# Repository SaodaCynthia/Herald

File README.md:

# Herald

Herald is a solar energy harvesting room number transmitter BLE beacon. It has been tested and deployed in 3 different indoor settings: a lab space with sunlight , indoor office with only indoor lights and an industrial steam plant with indoor lights. This project shows that solar energy harvesting beacons has promising future in indoor settings and performance can be further improved with planned deployment of beacons and a minimum indoor light intensity level.

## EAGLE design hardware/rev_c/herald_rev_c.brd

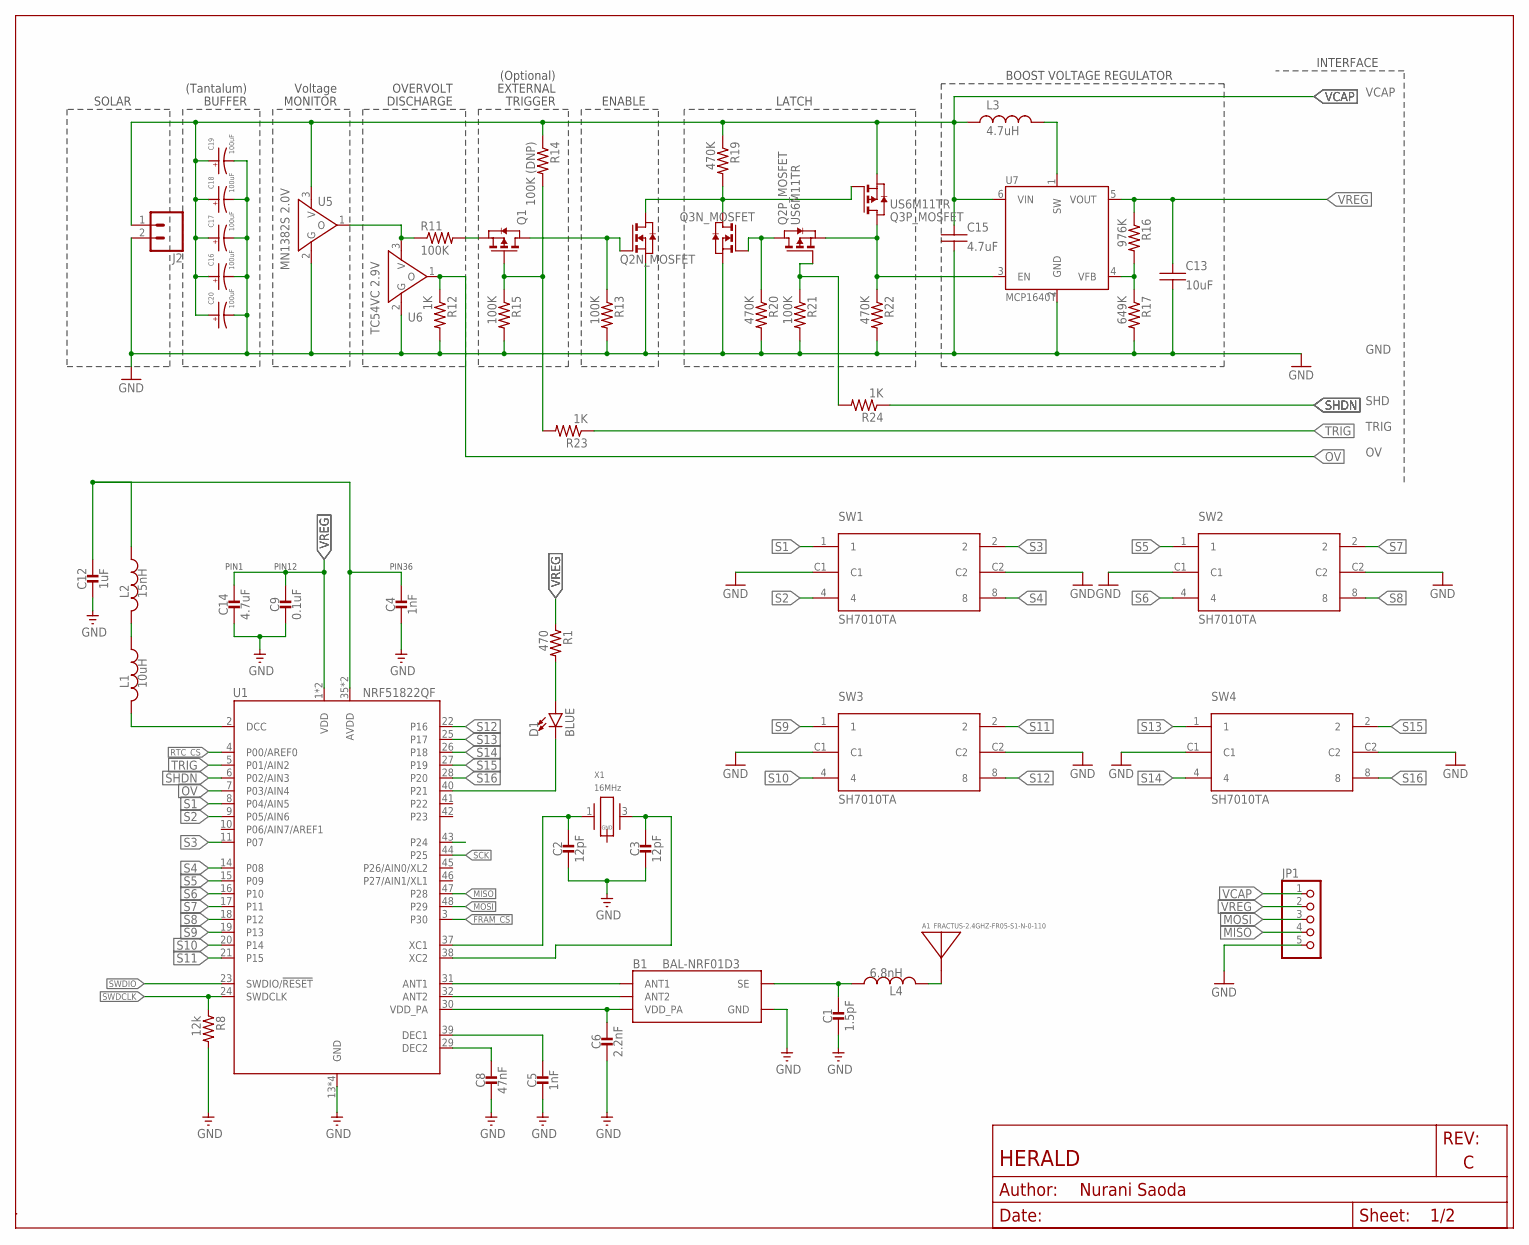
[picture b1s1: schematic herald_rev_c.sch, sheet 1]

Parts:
A1: FRACTUS-2.4GHZ-FR05-S1-N-0-110; FRACTUS-ANTENNA-FR05-S1-N-0-110
B1: BAL-NRF01D3
C1: 1.5pF; 0402_CAP
C2, C3: 12pF; 0402_CAP
C4, C5: 1nF; 0402_CAP
C6: 2.2nF; 0402_CAP
C8: 47nF; 0402_CAP
C9: 0.1uF; 0402_CAP
C12: 1uF; 0402_CAP
C13: 10uF; R0603B
C14: 4.7uF; 0402_CAP
C15: 4.7uF; R0603B
C16, C17, C18, C19, C20: 100uF; CAP1210
D1: BLUE; LED-0603
J2: CONN_02; 1X02
JP1: PINHD-1X5; 1X05
L1: 10uH; 0603_CAP; DIGIKEY 490-4025-1-ND
L2: 15nH; 0402_CAP; DIGIKEY 587-1521-1-ND
L3: 4.7uH; L2828
L4: 6.8nH; 0402_CAP; DIGIKEY 587-1521-1-ND
Q1: PMOSSOT23; SOT-23
Q2, Q3: US6M11TR; TUMT6
R1: 470; 0402_RES; DIGIKEY RHM470CECT-ND
R8: 12k; 0402_RES; DIGIKEY RHM12.0KCDCT-ND
R11, R13, R15, R21: 100K; R0603B
R12, R23, R24: 1K; R0603B
R14: 100K (DNP); R0603B
R16: 976K; R0603B
R17: 649K; R0603B
R19, R20, R22: 470K; R0603B
SW1, SW2, SW3, SW4: SH7010TA; SWTICH-6
U1: NRF51822QF; QFN-48-6MM; DIGIKEY 1490-1042-1-ND
U5: MN1382S 2.0V; MINI-3DC
U6: TC54VC 2.9V; MINI-3DC
U7: MCP1640T; SOT-23-6
X1: 16MHz; TXC-8Y; DIGIKEY 887-2003-1-ND

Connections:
!FRAM2_CS: U1.43 (P24)
!FRAM_CS: U1.3 (P30); also elsewhere on the board
GND: B1.GND, C1.2, C2.2, C3.2, C4.2, C5.2, C6.2, C8.2, C9.2, C12.2, C13.2, C14.2, C15.2, C16.ANODE, C17.ANODE, C18.ANODE, C19.ANODE, C20.ANODE, J2.2, JP1.5, Q2.1 (S), Q3.1 (S), R8.2, R12.2, R13.2, R15.2, R17.2, R20.2, R21.2, R22.2, SW1.C1, SW1.C2, SW2.C1, SW2.C2, SW3.C1, SW3.C2, SW4.C1, SW4.C2, U1.13 (GND), U1.33 (GND), U1.34 (GND), U1.GND, U5.2 (G), U6.2 (G), U7.2 (GND); also elsewhere on the board
MISO: JP1.4, U1.47 (P28); also elsewhere on the board
MOSI: JP1.3, U1.48 (P29); also elsewhere on the board
unnamed: A1.ANT, L4.2
unnamed: Q2.6 (D), Q3.5 (G), Q3.6 (D), R19.2
unnamed: B1.ANT1, U1.31 (ANT1)
unnamed: B1.ANT2, U1.32 (ANT2)
unnamed: D1.C, U1.40 (P21)
unnamed: D1.A, R1.2
unnamed: Q2.4 (S), Q3.3 (D), R22.1, U7.3 (EN)
unnamed: B1.SE, C1.1, L4.1
unnamed: C4.1, C12.1, L2.1, U1.35 (AVDD), U1.36 (AVDD)
unnamed: L1.2, U1.2 (DCC)
unnamed: L1.1, L2.2
unnamed: C2.1, U1.37 (XC1), X1.1
unnamed: C3.1, U1.38 (XC2), X1.3 (2)
unnamed: C5.1, U1.39 (DEC1)
unnamed: C8.1, U1.29 (DEC2)
unnamed: R16.2, R17.1, U7.4 (VFB)
unnamed: L3.2, U7.1 (SW)
unnamed: Q2.3 (D), Q3.2 (G), R20.1
unnamed: Q2.5 (G), R21.1, R24.2
unnamed: Q1.1 (D), Q2.2 (G), R13.1
unnamed: R11.1, U5.1 (O), U6.3 (V)
unnamed: Q1.3 (G), R14.2, R15.1, R23.2
unnamed: Q1.2 (S), R11.2
OV: R12.1, U1.7 (P03/AIN4), U6.1 (O)
RTC_CS: U1.4 (P00/AREF0); also elsewhere on the board
S1: SW1.1, U1.8 (P04/AIN5)
S2: SW1.4, U1.9 (P05/AIN6)
S3: SW1.2, U1.11 (P07)
S4: SW1.8, U1.14 (P08)
S5: SW2.1, U1.15 (P09)
S6: SW2.4, U1.16 (P10)
S7: SW2.2, U1.17 (P11)
S8: SW2.8, U1.18 (P12)
S9: SW3.1, U1.19 (P13)
S10: SW3.4, U1.20 (P14)
S11: SW3.2, U1.21 (P15)
S12: SW3.8, U1.22 (P16)
S13: SW4.1, U1.25 (P17)
S14: SW4.4, U1.26 (P18)
S15: SW4.2, U1.27 (P19)
S16: SW4.8, U1.28 (P20)
SCK: U1.44 (P25); also elsewhere on the board
SHDN: R24.1, U1.6 (P02/AIN3)
SWDCLK: R8.1, U1.24 (SWDCLK); also elsewhere on the board
SWDIO: U1.23 (SWDIO/!RESET); also elsewhere on the board
TRIG: R23.1, U1.5 (P01/AIN2)
VCAP: C15.1, C16.CATHODE, C17.CATHODE, C18.CATHODE, C19.CATHODE, C20.CATHODE, J2.1, JP1.1, L3.1, Q3.4 (S), R14.1, R19.1, U5.3 (V), U7.6 (VIN)
VDD_PA: B1.VCC (VDD_PA), C6.1, U1.30 (VDD_PA)
VREG: C9.1, C13.1, C14.1, JP1.2, R1.1, R16.1, U1.1 (VDD), U1.12 (VDD), U7.5 (VOUT); also elsewhere on the board

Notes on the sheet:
PIN12
PIN1
PIN36
VCAP
GND
SHD
TRIG
SOLAR
(Tantalum)
BUFFER
Voltage
MONITOR
OVERVOLT
DISCHARGE
EXTERNAL
TRIGGER
(Optional)
ENABLE
LATCH
BOOST VOLTAGE REGULATOR
INTERFACE

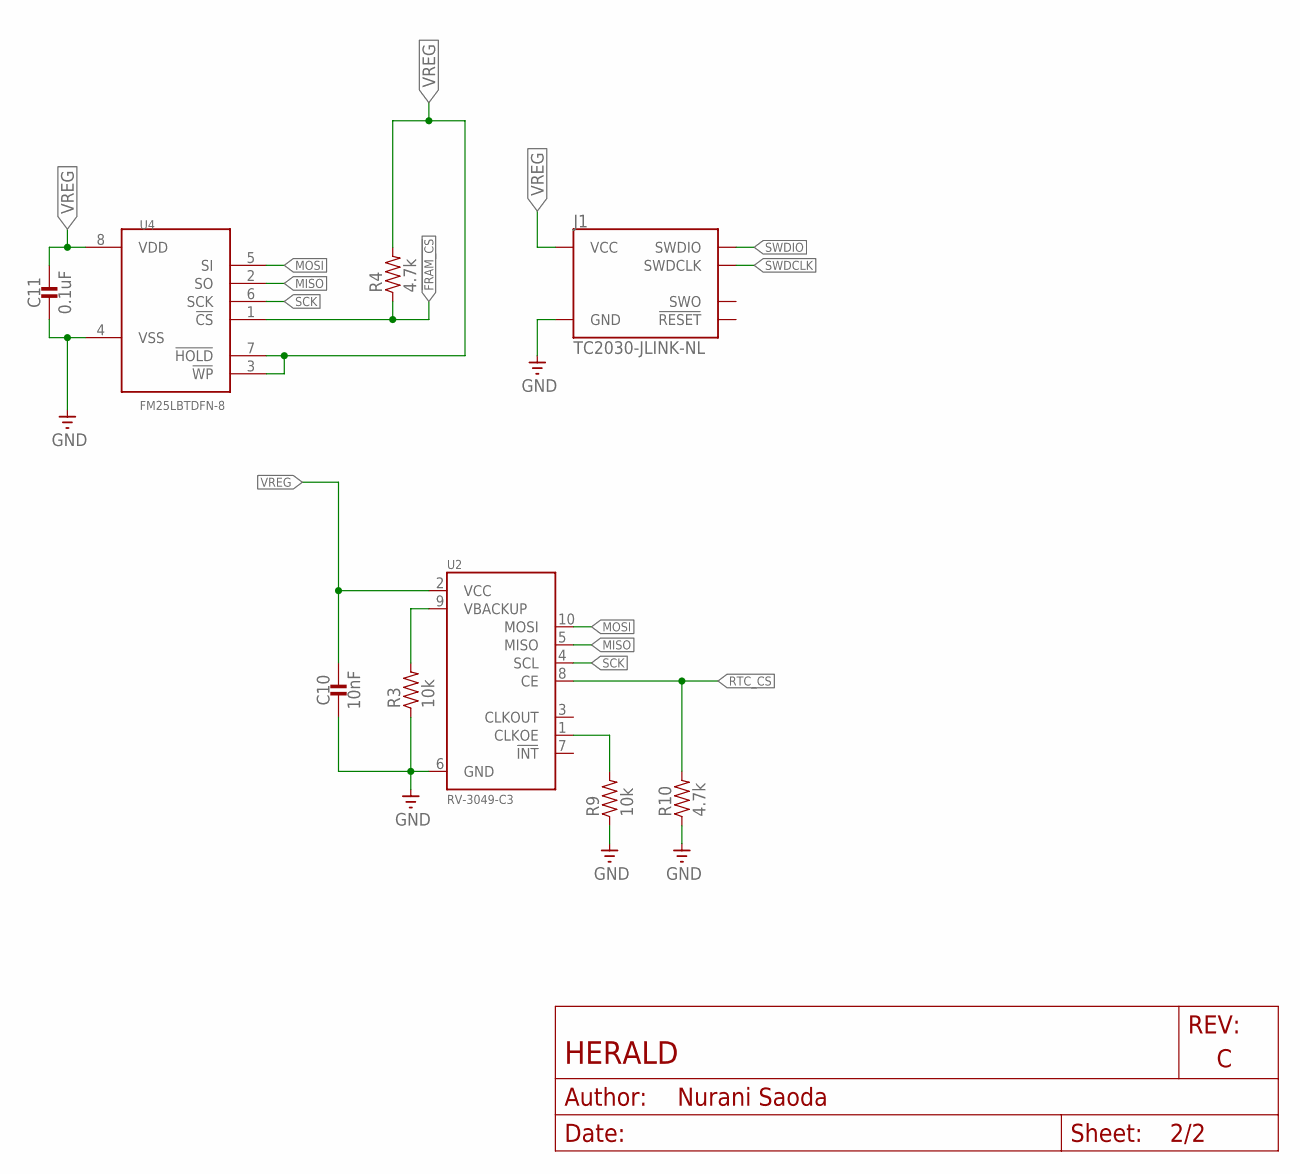
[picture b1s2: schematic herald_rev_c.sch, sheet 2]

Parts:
C10: 10nF; 0402_CAP
C11: 0.1uF; 0402_CAP
J1: TC2030-JLINK-NL; TC2030-IDC-NL
R3, R9: 10k; 0402_RES; DIGIKEY RHM10KCECT-ND
R4, R10: 4.7k; 0402_RES; DIGIKEY RHM4.7KCECT-ND
U2: RV-3049-C3; MICRO-CRYSTAL-C3
U4: FM25LBTDFN-8; TDFN-8@1; DIGIKEY FM25L04B-DGRA-ND

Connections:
!FRAM_CS: R4.1, U4.1 (!CS); also elsewhere on the board
GND: C10.2, C11.2, J1.5 (GND), R3.1, R9.1, R10.1, U2.6 (GND), U4.4 (VSS); also elsewhere on the board
MISO: U2.5 (MISO), U4.2 (SO); also elsewhere on the board
MOSI: U2.10 (MOSI), U4.5 (SI); also elsewhere on the board
unnamed: R3.2, U2.9 (VBACKUP)
unnamed: R9.2, U2.1 (CLKOE)
RTC_CS: R10.2, U2.8 (CE); also elsewhere on the board
SCK: U2.4 (SCL), U4.6 (SCK); also elsewhere on the board
SWDCLK: J1.4 (SWDCLK); also elsewhere on the board
SWDIO: J1.2 (SWDIO); also elsewhere on the board
VREG: C10.1, C11.1, J1.1 (VCC), R4.2, U2.2 (VCC), U4.3 (!WP), U4.7 (!HOLD), U4.8 (VDD); also elsewhere on the board

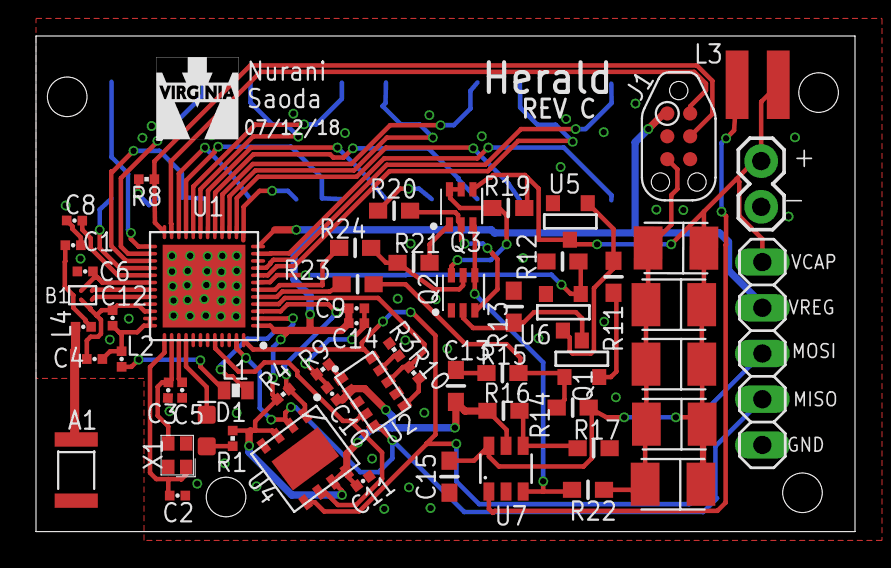
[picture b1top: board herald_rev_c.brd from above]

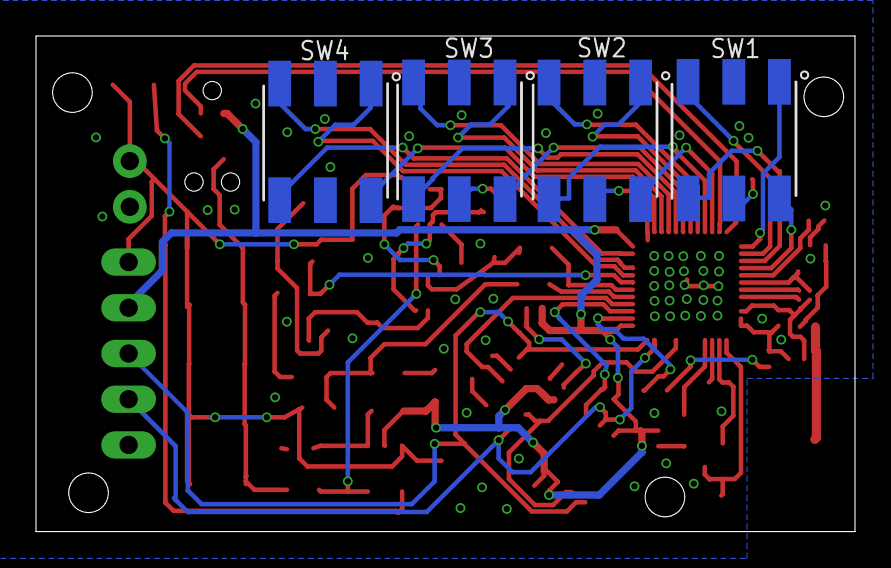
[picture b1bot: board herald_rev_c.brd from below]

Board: 2 copper layers, 45.5 x 27.5 mm, 62 parts (4 on the bottom side), 55 nets.

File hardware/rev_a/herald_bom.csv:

Partl,ist exported from C:/Users/ns8n,f/Documents/eagle/sensorfinal/s,ensor/sensor/sensor.sch at 5/29/,2018 3:27 PM
,,,,
Part,Value,Device,Package,Description                                                    DIGIKEY          MANUFACTURER       MOUSER               MPN               NEWARK     PROD_ID   RICHARDSON_RFPD VALUE
A1,FRACTUS-2.4GHZ-FR05-S1-N-0-110,FRACTUS-2.4GHZ-FR05-S1-N-0-110,FRACTUS-ANTENNA-FR05-S1-N-0-110,Fractus Micro Reach Xtend                                                                                                                                      FR05-S1-N-0110B
B1,BAL-NRF01D3,BAL-NRF01D3,BAL-NRF01D3,"50 ohm nominal input / conjugate match balun to nRF51422-QFAA, 497-13637-1-ND   STMicroelectronics 511-BAL-NRF01D3      BAL-NRF01D3"
C1,1.5pF,CAPACITOR0402_CAP,0402_CAP,SMD Capacitor
C2,12pF,CAPACITOR0402_CAP,0402_CAP,SMD Capacitor
C3,12pF,CAPACITOR0402_CAP,0402_CAP,SMD Capacitor
C4,1nF,CAPACITOR0402_CAP,0402_CAP,SMD Capacitor
C5,1nF,CAPACITOR0402_CAP,0402_CAP,SMD Capacitor
C6,2.2nF,CAPACITOR0402_CAP,0402_CAP,SMD Capacitor
C8,47nF,CAPACITOR0402_CAP,0402_CAP,SMD Capacitor
C9,0.1uF,CAPACITOR0402_CAP,0402_CAP,SMD Capacitor
C10,10nF,CAPACITOR0402_CAP,0402_CAP,SMD Capacitor
C11,0.1uF,CAPACITOR0402_CAP,0402_CAP,SMD Capacitor
C12,1uF,CAPACITOR0402_CAP,0402_CAP,SMD Capacitor
C13,10uF,CAP,R0603B,
C14,4.7uF,CAPACITOR0402_CAP,0402_CAP,SMD Capacitor
C15,4.7uF,CAP,R0603B,
C16,100uF,1210_CAP_POLARIZED,CAP1210,
C17,100uF,1210_CAP_POLARIZED,CAP1210,
C18,100uF,1210_CAP_POLARIZED,CAP1210,
C19,100uF,1210_CAP_POLARIZED,CAP1210,
C20,100uF,1210_CAP_POLARIZED,CAP1210,
D1,BLUE,LED-BLUE0603,LED-0603,Blue SMD LED                                                                                                                                         DIO-08575                 BLUE
J1,TC2030-JLINK-NL,TC2030-JLINK-NL,TC2030-IDC-NL,
JP1,,PINHD-1X6,1X06,PIN HEADER
JP2,,PINHD-1X2,1X02,PIN HEADER
L1,10uH,INDUCTOR0603,0603_CAP,A very specific inductor                                       490-4025-1-ND
L2,15nH,INDUCTOR0402,0402_CAP,A very specific inductor                                       587-1521-1-ND
L3,4.7uH,L-US,L2828,
L4,6.8nH,INDUCTOR0402,0402_CAP,A very specific inductor                                       587-1521-1-ND
Q1,,PMOSSOT23,SOT-23,MOS FET
Q2,US6M11TR,US6M11TR,TUMT6,US6M11CT-ND
Q3,US6M11TR,US6M11TR,TUMT6,US6M11CT-ND
R1,470,RESISTOR0402_RES,0402_RES,Resistor                                                       RHM470CECT-ND
R2,150,RESISTOR0402_RES,0402_RES,Resistor
R3,10k,RESISTOR0402_RES,0402_RES,Resistor                                                       RHM10KCECT-ND
R4,4.7k,RESISTOR0402_RES,0402_RES,Resistor                                                       RHM4.7KCECT-ND
R8,12k,RESISTOR0402_RES,0402_RES,Resistor                                                       RHM12.0KCDCT-ND
R9,10k,RESISTOR0402_RES,0402_RES,Resistor                                                       RHM10KCECT-ND
R10,4.7k,RESISTOR0402_RES,0402_RES,Resistor                                                       RHM4.7KCECT-ND
R11,100K,RESISTOR,R0603B,
R12,1K,RESISTOR,R0603B,
R13,100K,RESISTOR,R0603B,
R14,100K (DNP),RESISTOR,R0603B,
R15,100K,RESISTOR,R0603B,
R16,976K,RESISTOR,R0603B,
R17,649K,RESISTOR,R0603B,
R19,470K,RESISTOR,R0603B,
R20,470K,RESISTOR,R0603B,
R21,100K,RESISTOR,R0603B,
R22,470K,RESISTOR,R0603B,
R23,1K,RESISTOR,R0603B,
R24,1K,RESISTOR,R0603B,
S1,B3U-3000P-B,B3U-3000P-B,B3U-3000P-B,Switch                                                         SW1256CT-ND
SW1,SH7010TA,SH7010TA,SWTICH-6,563-1207-2-ND
SW2,SH7010TA,SH7010TA,SWTICH-6,563-1207-2-ND
SW3,SH7010TA,SH7010TA,SWTICH-6,563-1207-2-ND
SW4,SH7010TA,SH7010TA,SWTICH-6,563-1207-2-ND
U1,NRF51822QF,NRF51822QF,QFN-48-6MM,Multiprotocol Bluetooth« 4.0 low energy/2.4 GHz RF SoC         1490-1042-1-ND   Nordic Semi        949-NRF51822-QFAC-R7 NRF51822-QFAC-R7
U2,RV-3049-C3,RV-3049-C3,MICRO-CRYSTAL-C3,The RV-3049-C3 is an ultra miniature Real-Time-Clock Module                                                                               RV-3049-C3
U4,FM25LBTDFN-8,FM25LBTDFN-8,TDFN-8@1,IC FRAM 4KBIT 10MHZ 8SOIC                                      FM25L04B-DGRA-ND                     877-FM25L04B-DG
U5,MN1382S 2.0V,MN1382S,MINI-3DC,
U6,TC54VC 2.9V,MN1382S,MINI-3DC,
U7,MCP1640T,MCP1640,SOT-23-6,
X1,16MHz,TXC-8Y,TXC-8Y,2mmx1.6mm SMD Crystal                                          887-2003-1-ND

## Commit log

2018-05-29 Create herald
2018-05-29 Create del
2018-05-30 Create no
2018-05-30 /software/nrf5x-base
2018-05-30 Create a
2018-06-07 add parse.js
2018-06-07 add summon app
2018-06-11 cleaned up files
2018-06-13 changes in index
2018-06-14 Create rev_b
2018-06-28 main
2018-06-28 delay
2018-07-03 tuned timing properties
2018-07-03 none
2018-07-03 typos
2018-07-13 added sequence number
2018-09-21 r Please enter the commit message for your changes. Lines starting
2018-09-21 drivers updated:Wq
2019-06-04 resolved merge conflicts
2019-08-06 Added herald prototype picture and case

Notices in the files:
parts and their libraries:
SparkFun-LED: Licensing: Creative Commons ShareAlike 4.0 International - https://creativecommons.org/licenses/by-sa/4.0
